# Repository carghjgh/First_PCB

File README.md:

this is a very simple pcb and all it does is light up an LED, the reason i made this was to get used to kicad so i can start making more complex.

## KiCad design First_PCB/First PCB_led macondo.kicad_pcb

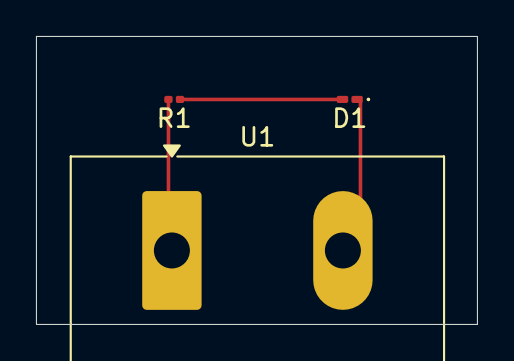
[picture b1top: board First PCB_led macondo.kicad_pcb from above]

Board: 2 copper layers, 24.5 x 16.0 mm, 3 parts (0 on the bottom side), 3 nets.

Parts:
D1: LED; LED_0201_0603Metric_Pad0.64x0.40mm_HandSolder
R1: 100; R_0201_0603Metric
U1: TerminalBlock_Ningbo-Kagnex_HB9500_1x02_P9.5mm

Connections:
GND: D1.1 (K), U1.2 (GRD)
unnamed: D1.2 (A), R1.1
unnamed: R1.2, U1.1 (PWR)

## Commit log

2026-05-08 First
2026-05-14 KICAD FILES
    this is where you can find the ki cad files
